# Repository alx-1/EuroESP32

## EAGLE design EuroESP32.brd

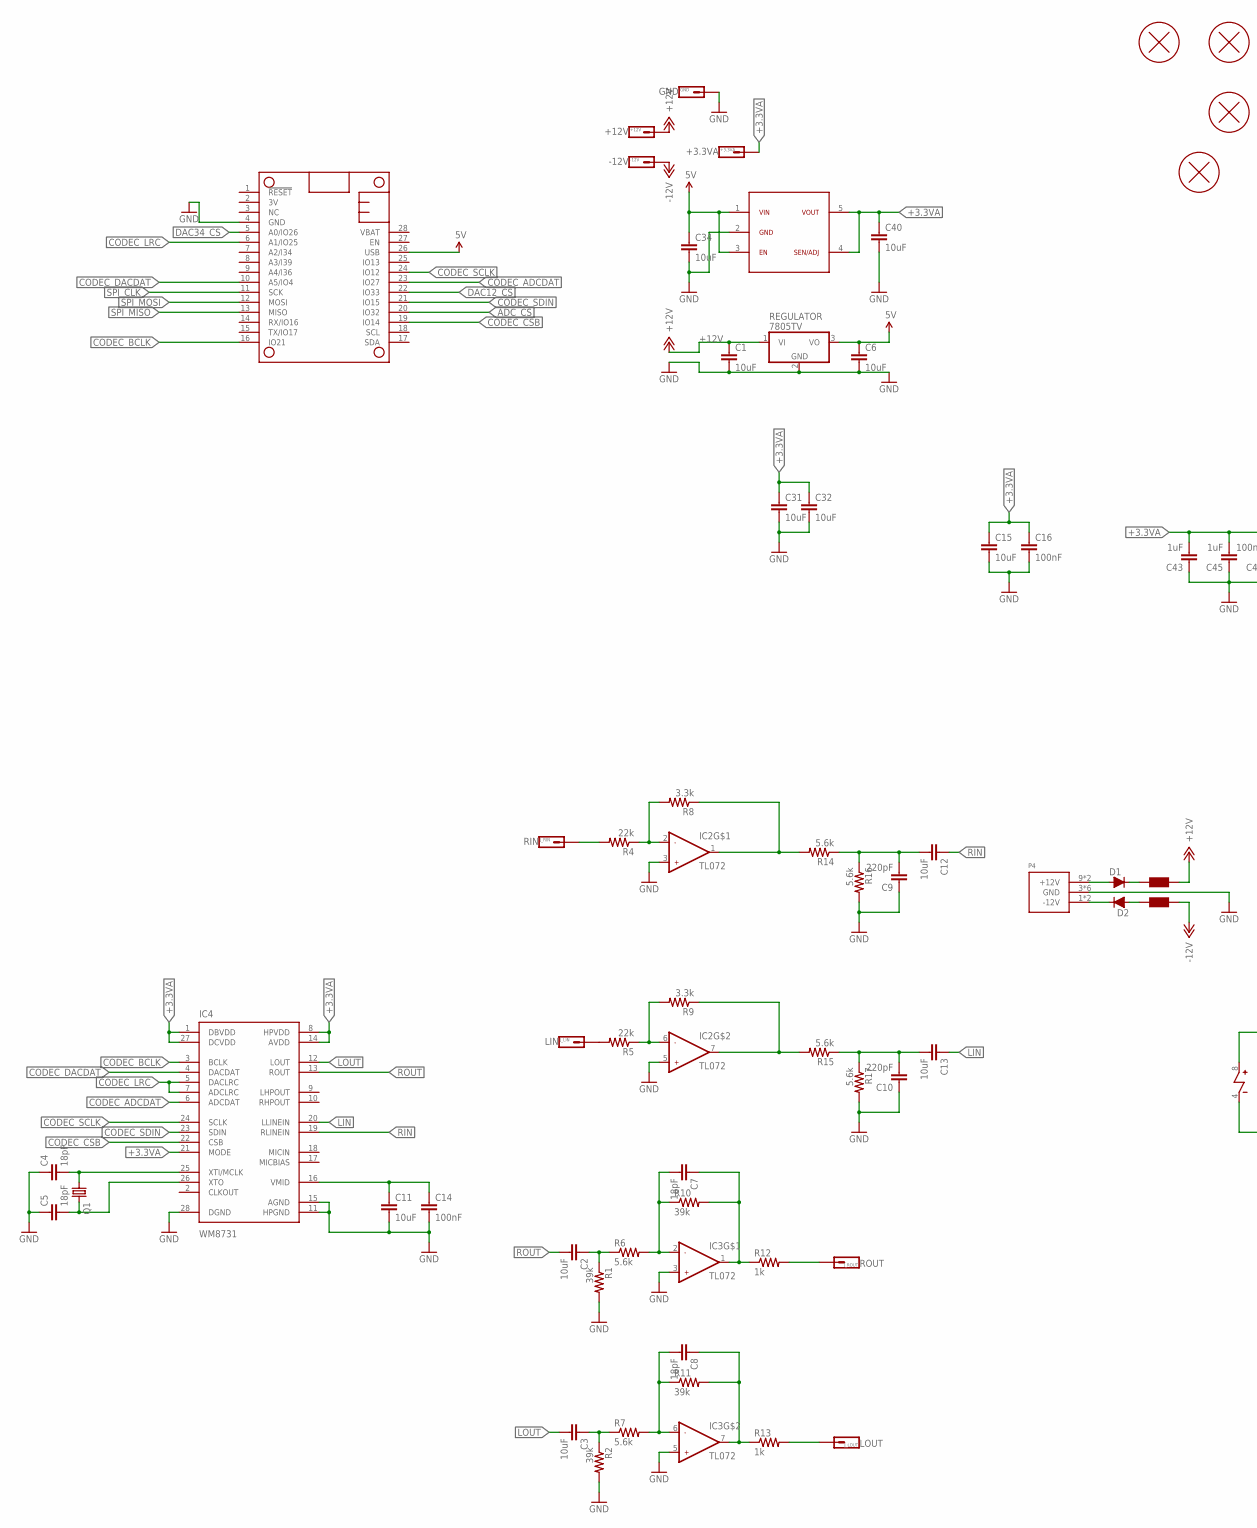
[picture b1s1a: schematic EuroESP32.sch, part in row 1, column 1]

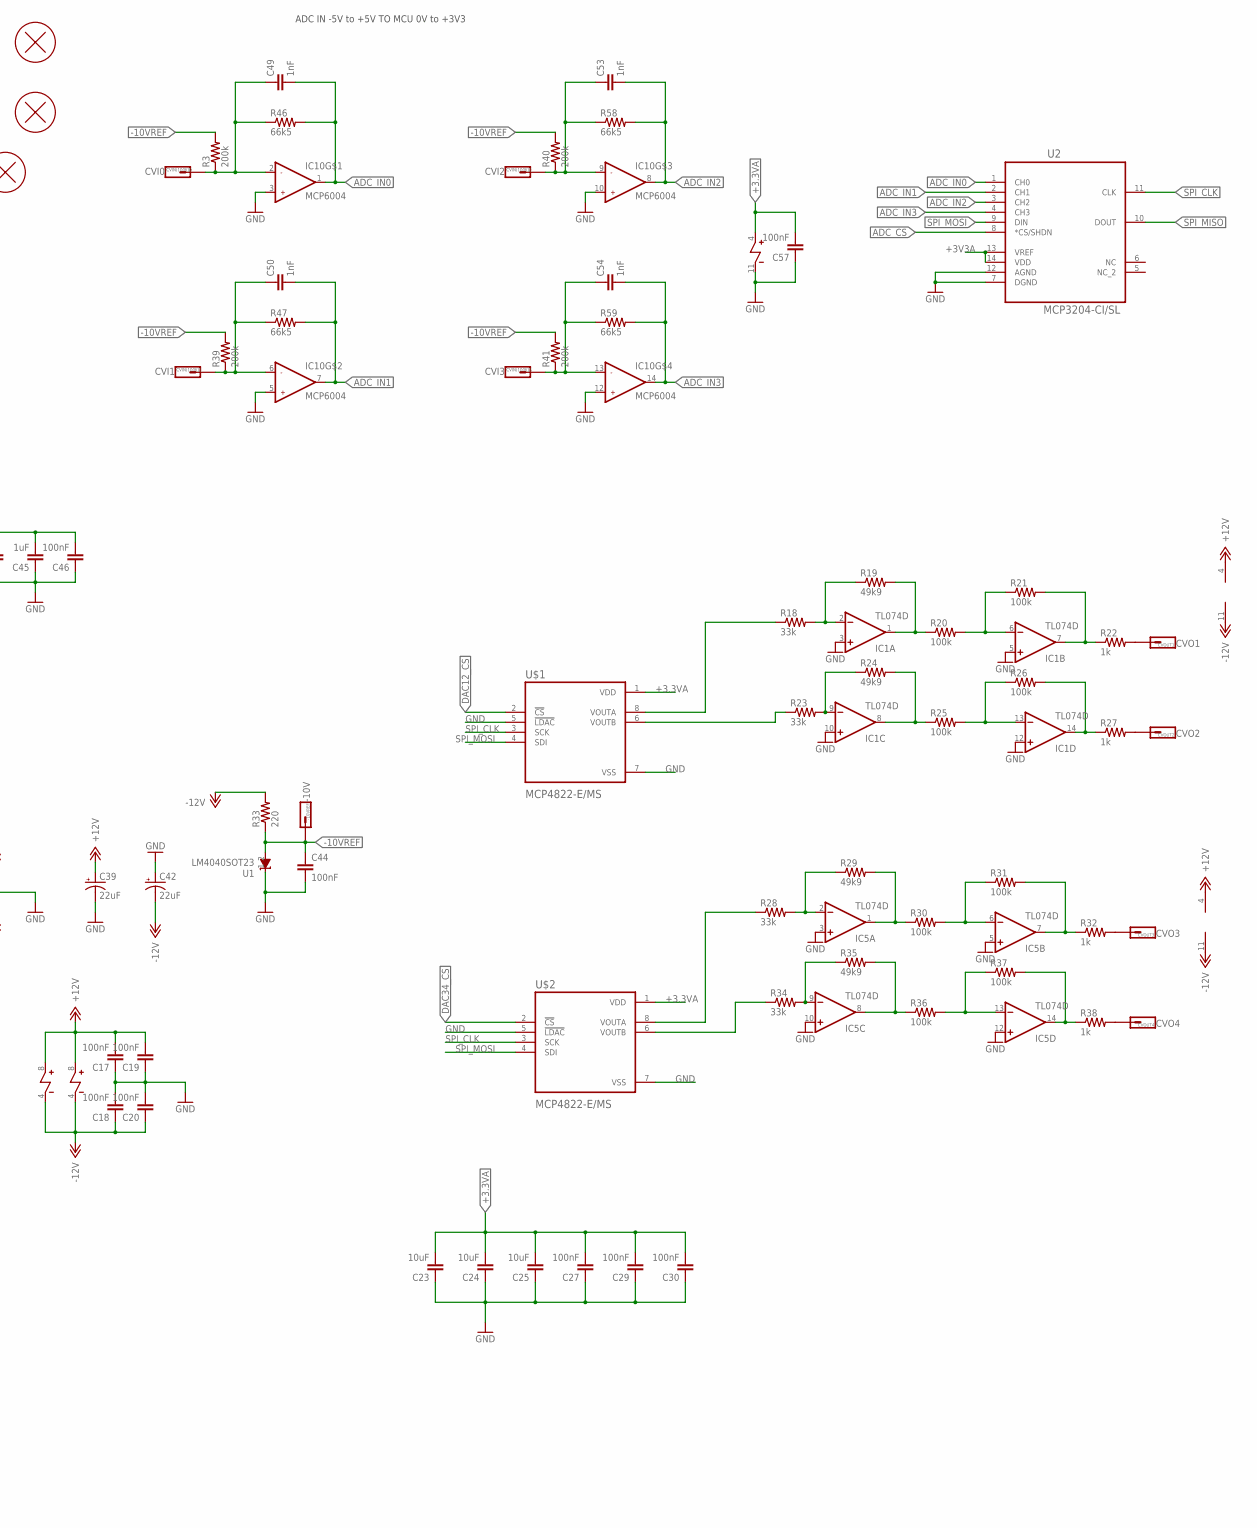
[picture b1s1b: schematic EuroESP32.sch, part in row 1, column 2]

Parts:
+3.3VA: +3.3VA; 1X01_SIDE_NAME
+12V: +12V; 1X01_SIDE_NAME
-10VREF: -10V; 1X01_SIDE_NAME
-12V: -12V; 1X01_SIDE_NAME
C1, C6: 10uF; C2.5-2
C2, C3, C11, C12, C13, C15, C23, C24, C25, C31, C32, C40: 10uF; R0805
C4, C5, C7, C8: 18pF; RESISTOR_0603
C9, C10: 220pF; RESISTOR_0603
C14, C16, C17, C18, C19, C20, C27, C29, C30, C44, C46, C57: 100nF; RESISTOR_0603
C34: 10uF; R1210
C39, C42: 22uF; 1206_POL
C43, C45: 1uF; RESISTOR_0603
C49, C50, C53, C54: 1nF; RESISTOR_0603
CVIN(100K)0: CVI0; 1X01_SIDE_NAME
CVIN(100K)1: CVI1; 1X01_SIDE_NAME
CVIN(100K)2: CVI2; 1X01_SIDE_NAME
CVIN(100K)3: CVI3; 1X01_SIDE_NAME
CVOUT1: CVO1; 1X01_SIDE_NAME
CVOUT2: CVO2; 1X01_SIDE_NAME
CVOUT3: CVO3; 1X01_SIDE_NAME
CVOUT4: CVO4; 1X01_SIDE_NAME
D1, D2: DIODE; SOD123
F1, F2: FERRITE-BEAD0805; R0805
GND: GND; 1X01_SIDE_NAME
H1, H3, H4, H5: PCB_SCREW
IC1, IC5: TL074D; SO14
IC2, IC3: TL072; SOIC8
IC4: WM8731; SSOP28
IC7: ADP7118; SOT23-5L
IC10: MCP6004; TSSOP14
J_LIN: LIN; 1X01_SIDE_NAME
J_LOUT: LOUT; 1X01_SIDE_NAME
J_RIN: RIN; 1X01_SIDE_NAME
J_ROUT: ROUT; 1X01_SIDE_NAME
MS2: FEATHER_HUZZAH32NO_DRILL; FEATHERWING_NODRILL
P4: POWER_SIMPLE10; POWER_10
Q1: CRYSTAL; HC49UP
R1, R2, R10, R11: 39k; RESISTOR_0603
R3, R39, R40, R41: 200k; RESISTOR_0603
R4, R5: 22k; RESISTOR_0603
R6, R7, R14, R15, R16, R17: 5.6k; RESISTOR_0603
R8, R9: 3.3k; RESISTOR_0603
R12, R13, R22, R27, R32, R38: 1k; RESISTOR_0603
R18, R23, R28, R34: 33k; RESISTOR_0603
R19, R24, R29, R35: 49k9; RESISTOR_0603
R20, R21, R25, R26, R30, R31, R36, R37: 100k; RESISTOR_0603
R33: 220; RESISTOR_0603
R46, R47, R58, R59: 66k5; RESISTOR_0603
REGULATOR: 7805TV; TO220V
U1: LM4040SOT23; SOT23
U2: MCP3204-CI/SL; SOIC127P600X175-14N
U$1, U$2: MCP4822-E/MS; SOP65P490X110-8N

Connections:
5V: C6.1, C34.1, IC7.1, IC7.3, MS2.26 (USB), REGULATOR.3 (VO)
+3.3VA: +3.3VA.1, C15.1, C16.1, C23.2, C24.2, C25.2, C27.2, C29.2, C30.2, C31.1, C32.1, C40.1, C43.2, C45.2, C46.2, C57.2, IC4.1 (DBVDD), IC4.8 (HPVDD), IC4.14 (AVDD), IC4.21 (MODE), IC4.27 (DCVDD), IC7.4, IC7.5, IC10.4, U$1.1 (VDD), U$2.1 (VDD)
+3V3A: U2.13 (VREF), U2.14 (VDD)
+12V: +12V.1, C1.1, C17.2, C19.2, C39.2 (+), F1.1, IC1.4 (V+), IC2.8, IC3.8, IC5.4 (V+), REGULATOR.1 (VI)
-10VREF: -10VREF.1, C44.1, R3.2, R33.1, R39.2, R40.2, R41.2, U1.2 (A)
-12V: -12V.1, C18.1, C20.1, C42.1 (-), F2.1, IC1.11 (V-), IC2.4, IC3.4, IC5.11 (V-), R33.2
ADC_CS: MS2.20 (IO32), U2.8 (*CS/SHDN)
ADC_IN0: C49.2, IC10.1, R46.2, U2.1 (CH0)
ADC_IN1: C50.2, IC10.7, R47.2, U2.2 (CH1)
ADC_IN2: C53.2, IC10.8, R58.2, U2.3 (CH2)
ADC_IN3: C54.2, IC10.14, R59.2, U2.4 (CH3)
CODEC_ADCDAT: IC4.6 (ADCDAT), MS2.23 (IO27)
CODEC_BCLK: IC4.3 (BCLK), MS2.16 (IO21)
CODEC_CSB: IC4.22 (CSB), MS2.19 (IO14)
CODEC_DACDAT: IC4.4 (DACDAT), MS2.10 (A5/IO4)
CODEC_LRC: IC4.5 (DACLRC), IC4.7 (ADCLRC), MS2.6 (A1/IO25)
CODEC_SCLK: IC4.24 (SCLK), MS2.24 (IO12)
CODEC_SDIN: IC4.23 (SDIN), MS2.21 (IO15)
DAC12_CS: MS2.22 (IO33), U$1.2 (!CS)
DAC34_CS: MS2.5 (A0/IO26), U$2.2 (!CS)
DAC_B: R23.1, U$1.6 (VOUTB)
DAC_D: R34.1, U$2.6 (VOUTB)
GND: C1.2, C4.1, C5.1, C6.2, C9.1, C10.1, C11.2, C14.2, C15.2, C16.2, C17.1, C18.2, C19.1, C20.2, C23.1, C24.1, C25.1, C27.1, C29.1, C30.1, C31.2, C32.2, C34.2, C39.1 (-), C40.2, C42.2 (+), C43.1, C44.2, C45.1, C46.1, C57.1, GND.1, IC1.3 (+IN), IC1.5 (+IN), IC1.10 (+IN), IC1.12 (+IN), IC2.3, IC2.5, IC3.3, IC3.5, IC4.11 (HPGND), IC4.15 (AGND), IC4.28 (DGND), IC5.3 (+IN), IC5.5 (+IN), IC5.10 (+IN), IC5.12 (+IN), IC7.2, IC10.3, IC10.5, IC10.10, IC10.11, IC10.12, MS2.4 (GND), P4.3 (GND), P4.4 (GND), P4.5 (GND), P4.6 (GND), P4.7 (GND), P4.8 (GND), R1.2, R2.2, R16.2, R17.2, REGULATOR.2 (GND), U1.1 (C), U2.7 (DGND), U2.12 (AGND), U$1.5 (!LDAC), U$1.7 (VSS), U$2.5 (!LDAC), U$2.7 (VSS)
LIN: C13.1, IC4.20 (LLINEIN)
LOUT: C3.2, IC4.12 (LOUT)
unnamed: J_LIN.1, R5.2
unnamed: J_LOUT.1, R13.2
unnamed: J_ROUT.1, R12.2
unnamed: IC1.2 (-IN), R18.2, R19.1
unnamed: IC1.7 (OUT), R21.2, R22.1
unnamed: IC1.9 (-IN), R23.2, R24.1
unnamed: IC1.1 (OUT), R19.2, R20.1
unnamed: IC1.14 (OUT), R26.2, R27.1
unnamed: IC5.6 (-IN), R30.2, R31.1
unnamed: IC1.8 (OUT), R24.2, R25.1
unnamed: IC5.2 (-IN), R28.2, R29.1
unnamed: IC5.7 (OUT), R31.2, R32.1
unnamed: IC5.13 (-IN), R36.2, R37.1
unnamed: C53.1, CVIN(100K)2.1, IC10.9, R40.1, R58.1
unnamed: IC5.1 (OUT), R29.2, R30.1
unnamed: C49.1, CVIN(100K)0.1, IC10.2, R3.1, R46.1
unnamed: IC5.9 (-IN), R34.2, R35.1
unnamed: C50.1, CVIN(100K)1.1, IC10.6, R39.1, R47.1
unnamed: IC5.14 (OUT), R37.2, R38.1
unnamed: C54.1, CVIN(100K)3.1, IC10.13, R41.1, R59.1
unnamed: IC1.6 (-IN), R20.2, R21.1
unnamed: IC5.8 (OUT), R35.2, R36.1
unnamed: R18.1, U$1.8 (VOUTA)
unnamed: CVOUT1.1, R22.2
unnamed: R28.1, U$2.8 (VOUTA)
unnamed: CVOUT2.1, R27.2
unnamed: IC1.13 (-IN), R25.2, R26.1
unnamed: CVOUT3.1, R32.2
unnamed: J_RIN.1, R4.2
unnamed: IC2.2, R4.1, R8.2
unnamed: D1.+, P4.9 (+12V), P4.10 (+12V)
unnamed: CVOUT4.1, R38.2
unnamed: IC2.1, R8.1, R14.2
unnamed: C9.2, C12.2, R14.1, R16.1
unnamed: IC2.6, R5.1, R9.2
unnamed: IC2.7, R9.1, R15.2
unnamed: C5.2, IC4.26 (XTO), Q1.2
unnamed: C4.2, IC4.25 (XTI/MCLK), Q1.1
unnamed: C10.2, C13.2, R15.1, R17.1
unnamed: C7.1, IC3.1, R10.2, R12.1
unnamed: D1.-, F1.2
unnamed: C7.2, IC3.2, R6.2, R10.1
unnamed: C2.1, R1.1, R6.1
unnamed: D2.-, P4.1 (-12V), P4.2 (-12V)
unnamed: C8.1, IC3.7, R11.2, R13.1
unnamed: C8.2, IC3.6, R7.2, R11.1
unnamed: C11.1, C14.1, IC4.16 (VMID)
unnamed: C3.1, R2.1, R7.1
unnamed: D2.+, F2.2
RIN: C12.1, IC4.19 (RLINEIN)
ROUT: C2.2, IC4.13 (ROUT)
SPI_CLK: MS2.11 (SCK), U2.11 (CLK), U$1.3 (SCK), U$2.3 (SCK)
SPI_MISO: MS2.13 (MISO), U2.10 (DOUT)
SPI_MOSI: MS2.12 (MOSI), U2.9 (DIN), U$1.4 (SDI), U$2.4 (SDI)

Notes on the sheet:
ADC IN -5V to +5V TO MCU 0V to +3V3

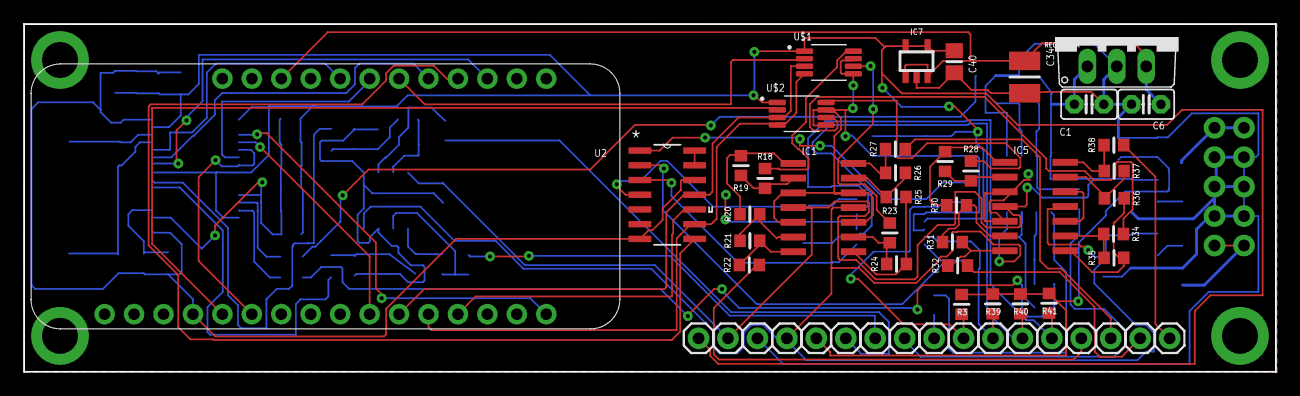
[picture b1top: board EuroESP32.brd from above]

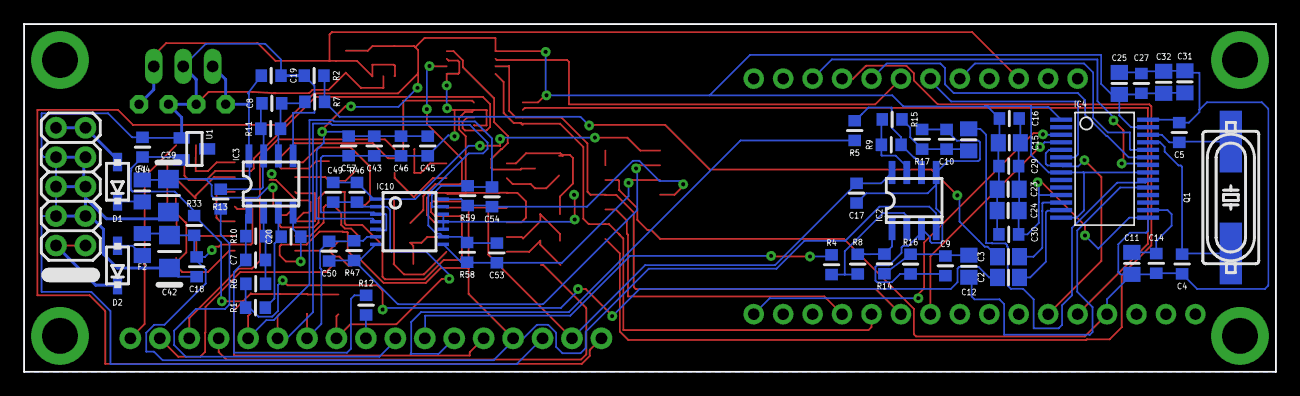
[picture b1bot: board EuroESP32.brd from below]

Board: 2 copper layers, 108.0 x 30.0 mm, 126 parts (69 on the bottom side), 79 nets.

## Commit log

2021-03-21 Plaquette redimensionnée
2021-03-22 v0.1
    TODO : TLC for the Labels

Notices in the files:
parts and their libraries:
SparkFun-Aesthetics: Licensing: Creative Commons ShareAlike 4.0 International - https://creativecommons.org/licenses/by-sa/4.0
